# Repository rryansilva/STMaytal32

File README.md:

# STMaytal32

STMaytal32 is a new generation proof-of-concept design for water pressure telemetry for underresourced water utilities. It uses a standard automotive oil pressure sender to read pressure and send this to a server where it can inform better operation of a utility. It follows up on the original proof-of-concept designed called Maytal and the designs and iterations that followed from Indonesian innovators supported by a grant from the USAID IUWASH Plus project.

This is just a proof-of-concept and should not be taken to be the right or best way to address the questions raised in the testing of earlier designs. 

## Design features
STMaytal32 responds to some challenges to scale that were identified in testing some of the earlier water pressure telemetry designs:

* *Modularity*. Earlier designs were integrated into one large box that was sometimes difficult to place near enough to a pipe outlet while still getting power and a communications signal. This led to some installations where very long cords were added to the pressure sender, changing the resistance and increasing the amount of power necessary to drive the sensor. STMaytal32 puts the sensing and computational functions in one box, and the communications function in another, independently powered box. This allows the two to be placed at a distance from one another without interfering with readings or signal (provided the UART signal between the two remains readable). It also enables different communications technologies to be used in different installation contexts.
* *Bill of Materials*. The STMaytal32 design is centered on the "Blue Pill" STM32 development board which is common in Indonesia (IDR 70,000 on Tokopedia) and on the worldwide market (US$1.48 on Aliexpress). The Blue Pill includes an oscillator to drive the onboard RTC peripheral, obviating the need for a separate RTC to wake the unit from sleep. Efforts have been taken to reduce extraneous hardware that would add cost to the design. 
* *Power*. Field placement of earlier designs revealed that in practice, utilities often want to position these units in places such as in manholes or among complex piping systems that do not readily allow for solar or mains power. By using the relatively power-efficient STM32 and eliminating unnecessary hardware, the main module of the STMaytal32 can be powered by 4 AA batteries, which should run the unit for several months before needing replacement. 
* *Communications*. Earlier designs used GSM networks for communications, which, while effective, would impose operating costs and administrative burden for utilities. The communications module described here uses LoRaWAN for communications, which should enable utilities to manage their own simple, inexpensive networks which can also be used to collect data from future sensors.

## Breakdown
### Core module

1. *1x03 connector*. To enable the pressure sender to be easily attached and detached.
2. *Serial1 breakout.* Pins to the STM32's Serial1 port are broken out here to facilitate debugging.
3. *Smoothing capacitors*. To reduce variations in supply from the AA batteries.
4. *Voltage divider*. To convert the 5V signal from the pressure sender to a 3.3V equivalent signal.
5. *Voltage regulator*. The regulator on the Blue Pill supplies 3.3V of dubious reliability. This supplies 5V direct from the AA batteries.
6. *Power MOSFET*. Cuts power to the pressure sender while not in use.
7. *"Blue Pill" STM32 development board*. Note that the PWR LED has been desoldered to save power.
8. *1x10 JTAG-style connector*. To connect to a GX16-10 aviation connector on the enclosure, which connects this with the communications module.

### Communications module

The communications module is just an Adafruit RFM9x LoRa breakout board and an Adafruit Solar LiPo charger board, interfaced with a 1x10 JTAG-style connector to facilitate connection to the core module. More work to source locally-appropriate and less expensive parts is called for in the near future.

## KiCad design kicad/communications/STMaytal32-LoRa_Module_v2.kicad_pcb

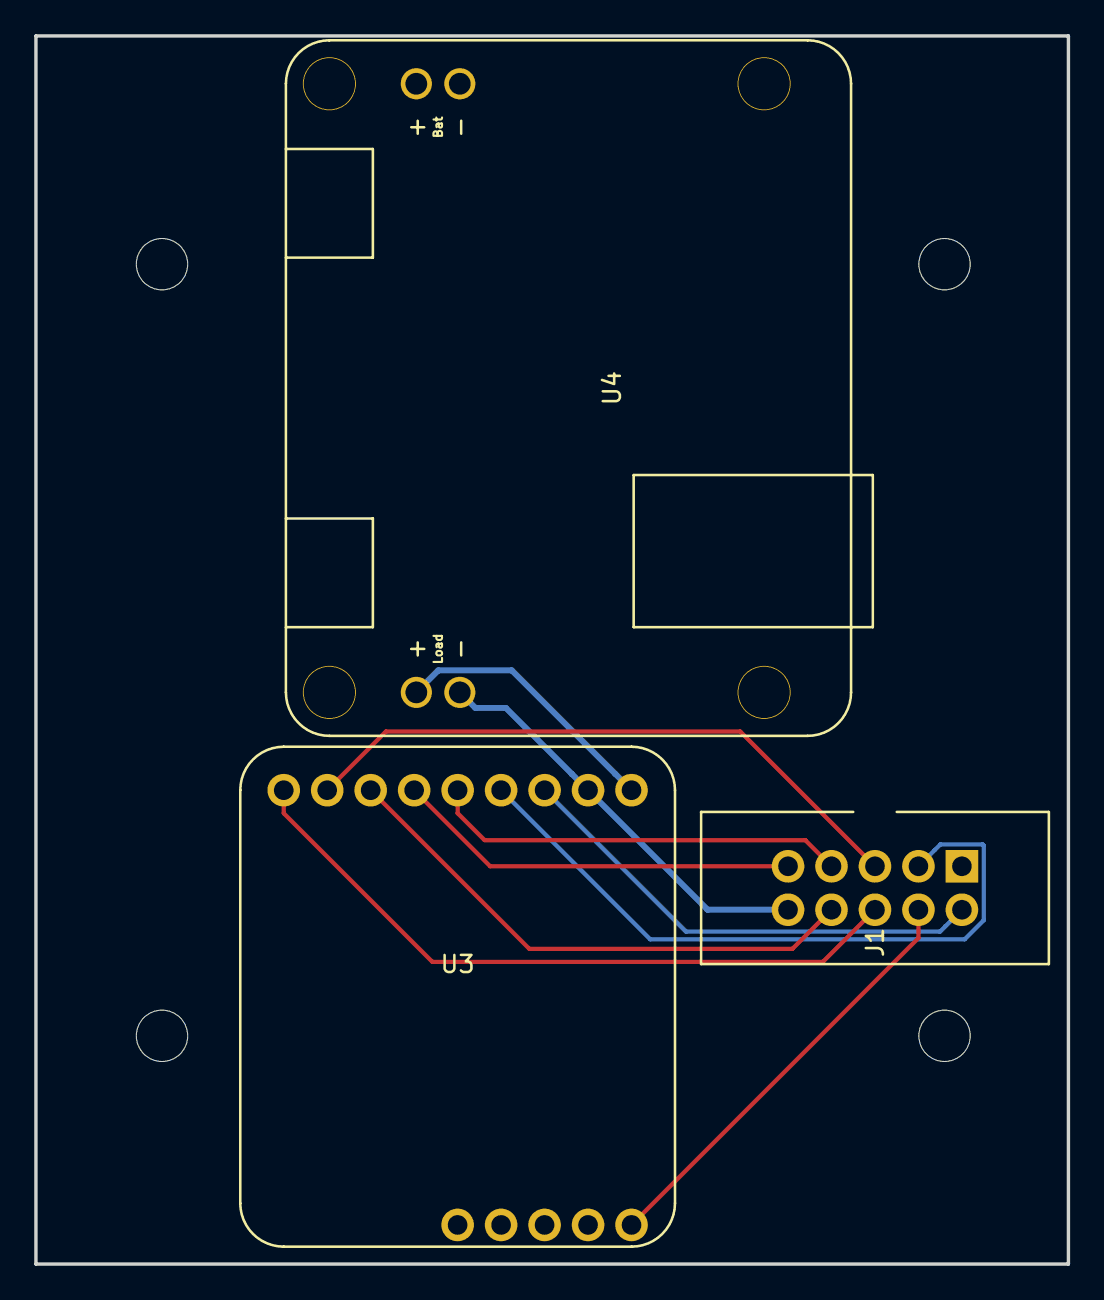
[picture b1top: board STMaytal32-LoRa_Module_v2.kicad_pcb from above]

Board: 2 copper layers, 60.3 x 71.8 mm, 3 parts (0 on the bottom side), 10 nets.

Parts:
J1: Conn_02x05_Counter_Clockwise; 2x05-JTAG-type-connector
U3: Adafruit_LoRa_Breakout
U4: Adafruit_LiPoly_Solar; Adafruit_LiPo_Solar

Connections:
CS-RI: J1.5, U3.8
EN: J1.2, U3.3
G0: J1.3, U3.5
G1-PSTAT: J1.4, U3.10
GND: J1.10, U3.2, U4.4
MISO-TX: J1.9, U3.6
MOSI-KEY: J1.8, U3.7
unnamed: U3.1, U4.3
RST: J1.6, U3.9
SCK-RX: J1.7, U3.4

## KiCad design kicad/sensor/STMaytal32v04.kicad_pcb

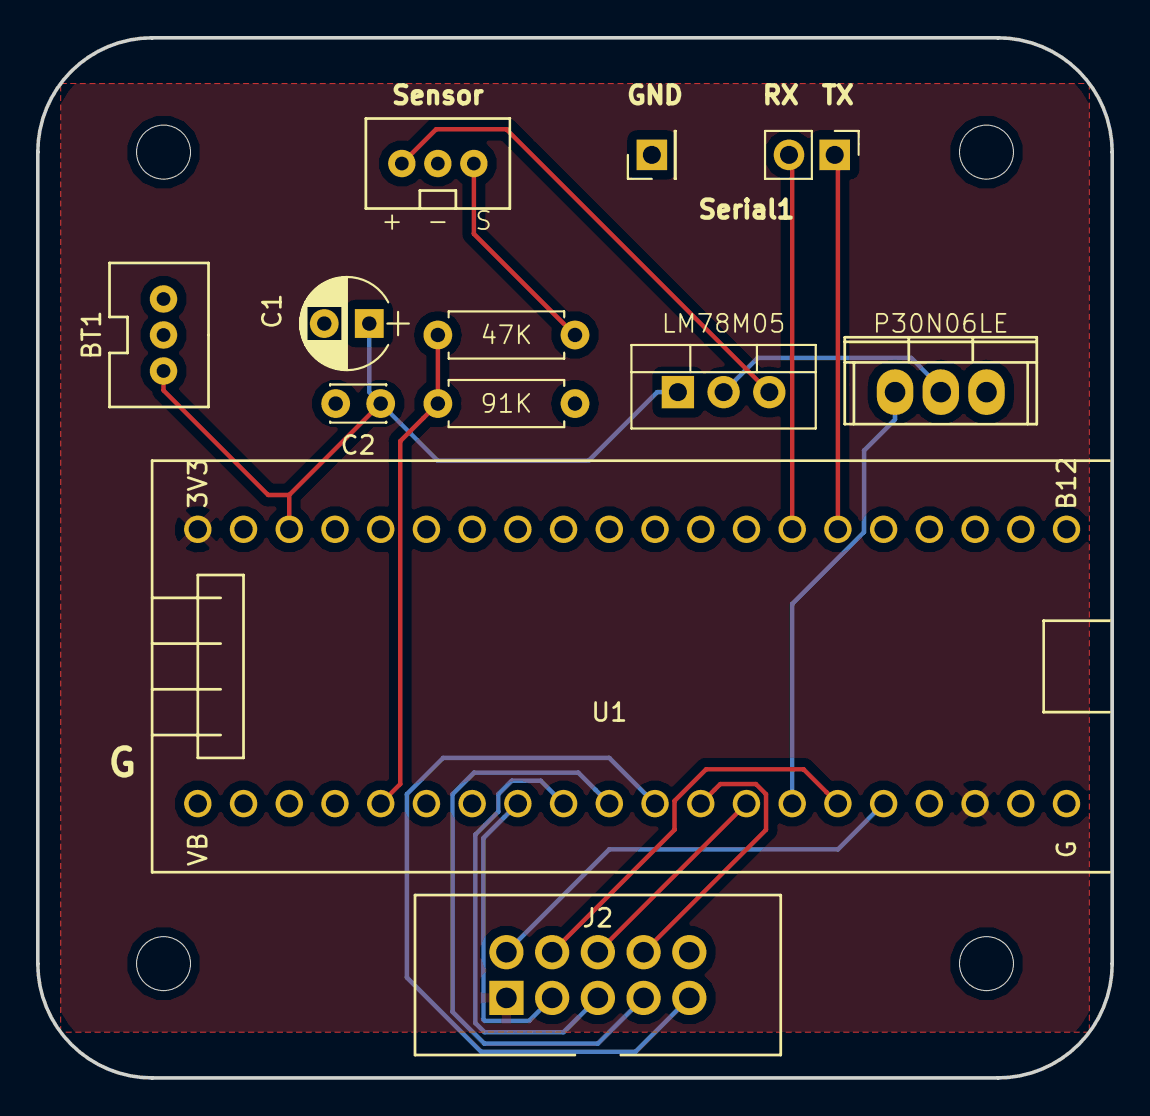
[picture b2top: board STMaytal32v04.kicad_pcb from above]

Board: 2 copper layers, 59.7 x 57.8 mm, 12 parts (0 on the bottom side), 18 nets.

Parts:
BT1: Battery; Keystone_3POS_2mm
C1: 10uF; CP_Radial_D5.0mm_P2.50mm
C2: 0.1uF; C_Disc_D3.0mm_W2.0mm_P2.50mm
J1: Conn_01x03_Male; JST-PH-2.0-3_pin
J2: Conn_02x05_Counter_Clockwise; 2x05-JTAG-type-connector
J3: Conn_01x01_Male; Pin_Header_Straight_1x01_Pitch2.54mm
J4: Conn_01x02_Male; Pin_Header_Straight_1x02_Pitch2.54mm
Q1: P30N06LE; TO-220
R1: 47K; R_Axial_DIN0207_L6.3mm_D2.5mm_P7.62mm_Horizontal
R2: 91K; R_Axial_DIN0207_L6.3mm_D2.5mm_P7.62mm_Horizontal
U1: STM32_Blue_Pill
U2: LM78M05_TO220; TO-220-3_Vertical

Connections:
CS-RI: J2.5, U1.14
EN: J2.2, U1.22
G0: J2.3, U1.13
G1-PSTAT: J2.4, U1.21
GND: BT1.1, C1.2, C2.2, J1.2, J2.10, J3.1, Q1.3, R2.2, U1.GND
MISO-TX: J2.9, U1.16
MOSI-KEY: J2.8, U1.17
unnamed: J1.1, U2.3
unnamed: J1.3, R1.1
unnamed: Q1.2, U2.2
PRESSURE: R1.2, R2.1, U1.10
Q1_BASE: Q1.1, U1.19
RST: J2.6, U1.18
SCK-RX: J2.7, U1.15
SERIAL1.RX: J4.2, U1.31
SERIAL1.TX: J4.1, U1.30
VBAT: BT1.3, C1.1, C2.1, U1.5V, U2.1
VCC: J2.1, U1.3V3

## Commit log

2019-02-08 Upload source code
2019-02-22 Pressure reading now works
2019-02-22 Removed reference to pressure readings not working
2019-04-02 Updated board footprints
2019-04-02 DS_Store banished
